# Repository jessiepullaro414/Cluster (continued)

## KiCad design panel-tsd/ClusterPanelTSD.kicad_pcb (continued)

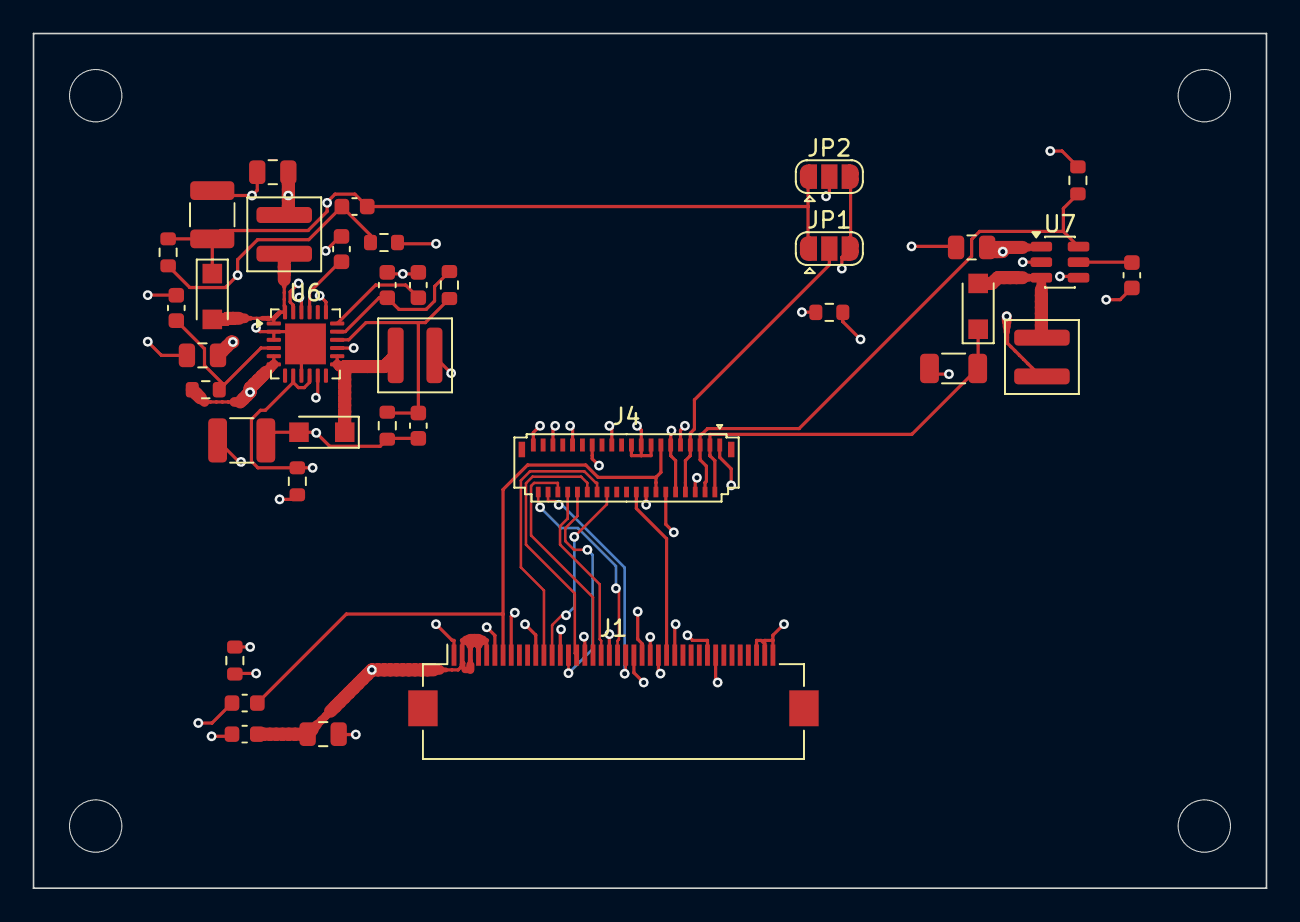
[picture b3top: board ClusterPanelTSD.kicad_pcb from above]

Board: 6 copper layers, 75.4 x 52.3 mm, 41 parts (0 on the bottom side), 32 nets.

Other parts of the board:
MH1, MH2, MH3, MH4: MountingHole_3.2mm_M3

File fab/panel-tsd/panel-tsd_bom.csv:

Manufacturer Part Number,Manufacturer,Quantity,Designators,Package,Category,Description,Status
PMEG6010ELRX,Nexperia,3,D2-D4,Nexperia_CFP3_SOD-123W,Semiconductors,"Boost rectifier Schottky, 60V/1A, SOD-123W",ok
(no part - PCB footprint only),-,2,"JP1, JP2",SolderJumper-3_P1.3mm_Open_RoundedPad1.0x1.5mm,Semiconductors,3-pad OPEN solder jumper (KiCad SolderJumper-3_P1.3mm_Open_RoundedPad1.0x1.5mm); bridged with a solder blob after verifying the panel's +/-6.5V pin polarity - see JP1/JP2 in build_schematic.py,ok
XAL4030-472MEC,Coilcraft,2,"L2, L3",L_Coilcraft_XAL4030-XXX,Semiconductors,"4.7uH shielded molded power inductor, Isat 4.6A, DCR 40mR typ, 4x4x3mm (datasheet Document 806-1; trailing C = 7in reel ordering code)",ok
TPS61165TDBVRQ1,TI,1,U7,SOT-23-6,Semiconductors,"Automotive boost white-LED driver, panel backlight 15V/180mA from +5V with PWM dimming, SOT-23-6 DBV (datasheet SLVSB73B); TI lists the family Active. Orderable suffix taken from a TI E2E thread and a datasheet listing - confirm on TI's store",ok
TPS65131TRGERQ1,TI,1,U6,HVQFN-24-1EP_4x4mm_P0.5mm_EP2.5x2.5mm,Semiconductors,"Automotive dual-output boost + inverting LCD bias supply, panel +6.5V/-6.5V analog rails from +5V, VQFN-24 RGE with wettable flanks (datasheet SLVSBB2F); TI lists it Active",ok
XAL4040-103MEC,Coilcraft,1,L4,L_Coilcraft_XAL4040-XXX,Semiconductors,"10uH shielded molded power inductor, Isat 3.0A, DCR 84mR typ, 4x4x4mm (datasheet Document 806-1; trailing C = 7in reel ordering code)",ok
FH12-40S-0.5SH(55),Hirose,1,J1,Hirose_FH12-40S-0.5SH_1x40-1MP_P0.50mm_Horizontal,Connectors,"Port input from the brain board's screen port A (MIPI DSI): 40-position 0.5 mm-pitch FFC connector, the same part as the brain board's J4, pin order in tools/screen_ports.py. PATTERN: confirm the (55) reel suffix and the 0.5 A per-contact rating in the cart",ok
FH26-39S-0.3SHW(99),Hirose,1,J4,Hirose_FH26-39S-0.3SHW_2Rows-39Pins-1MP_P0.60mm_Horizontal,Connectors,"39-position 0.3mm-pitch FPC connector for the TST040HDBC-42's 39-pin FPC. The panel datasheet does NOT name a connector: 0.3mm pitch is inferred from the FPC's 12mm width across 39 pins, and FH26 is bottom-contact - specify the FPC's exposed-pad side when ordering from TSD. Hirose lists the (05) variant obsolete and FH26W-39S-0.3SHW(60) as current: confirm its land pattern against the bundled FH26 footprint before ordering",ok
"FFC, 40-way 0.5 mm pitch, about 100-150 mm long (PATTERN: e.g. Molex 15015 series)",Molex / Wurth (TBD),1,J1 to the brain board's J4,FFC cable,Companion parts (ordered separately),The ribbon to the brain board's screen port A (it is listed on the brain board's BOM too: buy one per screen). Choose the contact orientation that joins contact n to contact n,ok
Team Source Display TST040HDBC-42,Team Source Display (TSD),1,plugs into J4,FPC module,Companion parts (ordered separately),"4.0in 720x720 round IPS, native MIPI-DSI (3 lanes), ICNL9707 driver built into the module, 800 cd/m2, -30..+80C, 101.52mm active circle - datasheet V1.0 (2023-06-29) read in full; connects via J4 above, not its own BOM line. Datasheet table and drawing DISAGREE on which FPC pins carry +6.5V vs -6.5V - resolve with TSD before bridging JP1/JP2. Order the FPC with the exposed-pad side matching J4's bottom-contact. ORDER FROM TSD (not a stocked distributor part): request the FPC with contact fingers matching J4 (Hirose FH26 is bottom-contact) and ask the questions in docs/rfq-drafts.md first",ok
AC0603FR-07100KL,Yageo,3,"R41, R43, R50",R_0603_1608Metric,Passives,"Resistor 100k 1% 0603 thick film, AEC-Q200 [PATTERN: confirm this exact part number in the distributor cart]",PATTERN: confirm in cart
GCM188R71H104KA57D,Murata,3,"C2, C3, C42",C_0603_1608Metric,Passives,"Capacitor, 100 nF X7R 50 V, AEC-Q200",ok
GCM188R71H224KA64D,Murata,2,"C43, C51",C_0603_1608Metric,Passives,"Capacitor, 220 nF X7R 50 V, AEC-Q200",ok
GCM21BR71A106KE22L,Murata,2,"C1, C50",C_0805_2012Metric,Passives,"Capacitor, 10 uF X7R 10 V, AEC-Q200",ok
GCM21BR71C475KA73L,Murata,2,"C40, C41",C_0805_2012Metric,Passives,"Capacitor, 4.7 uF X7R 16 V, AEC-Q200",ok
GCM32ER71C226ME19L,Murata,2,"C46, C47",C_1210_3225Metric,Passives,"Capacitor, 22 uF X7R 16 V, AEC-Q200",ok
AC0603FR-07100RL,Yageo,1,R37,R_0603_1608Metric,Passives,"Resistor 100R 1% 0603 thick film, AEC-Q200 [PATTERN: confirm this exact part number in the distributor cart]",PATTERN: confirm in cart
AC0603FR-07130KL,Yageo,1,R39,R_0603_1608Metric,Passives,"Resistor 130k 1% 0603 thick film, AEC-Q200 [PATTERN: confirm this exact part number in the distributor cart]",PATTERN: confirm in cart
AC0603FR-071R1L,Yageo,1,R42,R_0603_1608Metric,Passives,"Resistor 1R1 1% 0603 thick film, AEC-Q200 [PATTERN: confirm this exact part number in the distributor cart]",PATTERN: confirm in cart
AC0603FR-072KL,Yageo,1,R1,R_0603_1608Metric,Passives,"Resistor 2k 1% 0603 thick film, AEC-Q200 [PATTERN: confirm this exact part number in the distributor cart]",PATTERN: confirm in cart
AC0603FR-07499KL,Yageo,1,R40,R_0603_1608Metric,Passives,"Resistor 499k 1% 0603 thick film, AEC-Q200 [PATTERN: confirm this exact part number in the distributor cart]",PATTERN: confirm in cart
AC0603FR-07511KL,Yageo,1,R38,R_0603_1608Metric,Passives,"Resistor 511k 1% 0603 thick film, AEC-Q200 [PATTERN: confirm this exact part number in the distributor cart]",PATTERN: confirm in cart
GCJ31CC71H475KA01L,Murata,1,C52,C_1206_3216Metric,Passives,"Capacitor, 4.7 uF X7R 50 V, AEC-Q200",ok
GCM1885C1H120JA16D,Murata,1,C48,C_0603_1608Metric,Passives,"Capacitor, 12 pF C0G 50 V, AEC-Q200",ok
GCM1885C1H150JA16D,Murata,1,C49,C_0603_1608Metric,Passives,"Capacitor, 15 pF C0G 50 V, AEC-Q200 [PATTERN: confirm this exact part number in the distributor cart]",PATTERN: confirm in cart
GCM188R71H103KA37D,Murata,1,C44,C_0603_1608Metric,Passives,"Capacitor, 10 nF X7R 50 V, AEC-Q200",ok
GCM188R71H472KA37D,Murata,1,C45,C_0603_1608Metric,Passives,"Capacitor, 4.7 nF X7R 50 V, AEC-Q200",ok

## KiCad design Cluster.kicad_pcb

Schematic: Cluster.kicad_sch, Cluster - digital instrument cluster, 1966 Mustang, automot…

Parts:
C1: 10uF X7R (AEC-Q200); C_0603_1608Metric
C2: 22uF X7R (AEC-Q200); C_0603_1608Metric
C3: 1uF X7R (AEC-Q200); C_0603_1608Metric
C4, C5, C23, C24: 18pF (AEC-Q200); C_0603_1608Metric
C6, C7: 100nF (AEC-Q200); C_0603_1608Metric
C8: 1uF (AEC-Q200); C_0603_1608Metric
C10: 100nF charge-pump cap (AEC-Q200); C_0603_1608Metric
C11: 100nF BOOT cap (AEC-Q200); C_0603_1608Metric
C12: 1uF VCC decouple (AEC-Q200); C_0603_1608Metric
C13, C25: 100nF VCC decouple (AEC-Q200); C_0603_1608Metric
C14: 100nF VIO decouple (AEC-Q200); C_0603_1608Metric
C15: 100nF VBAT decouple (AEC-Q200); C_0603_1608Metric
C16: 4.7nF SPLIT stabilization (AEC-Q200); C_0603_1608Metric
C17, C18, C19, C20: 100nF VCI decouple (AEC-Q200); C_0603_1608Metric
C21: 10uF IN cap (AEC-Q200); C_0603_1608Metric
C22: 10uF OUT cap, real min 2.2uF per TI's own stabili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; C_0603_1608Metric
C26: 1uF VCC1V2 decouple (AEC-Q200); C_0603_1608Metric
C27: 100nF VCCIO decouple (AEC-Q200); C_0603_1608Metric
C28: 100nF ADC_FUEL smoothing (AEC-Q200); C_0603_1608Metric
C29: 100nF ADC_OIL smoothing (AEC-Q200); C_0603_1608Metric
C30: 100nF ADC_TEMP smoothing (AEC-Q200); C_0603_1608Metric
C31: 100nF ADC_BATT smoothing (AEC-Q200); C_0603_1608Metric
D1: SMCJ33A automotive (AEC-Q101); D_SMC
F1: Mini blade holder, 2A Littelfuse 297 fuse (SAE J2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; Fuseholder_Blade_Mini_Keystone_3568
J1: DTM06-2S nickel, 12V input (sealed); TerminalBlock_Phoenix_MKDS-1,5-2-5.08_1x02_P5.08mm_Horizont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
J2: SWD Tag-Connect; Tag-Connect_TC2030-IDC-NL_2x03_P1.27mm_Vertical
J3: Panox BH021WVC02 - center speedo; Amphenol_F32Q-1A7x1-11040_1x40-1MP_P0.5mm_Horizontal
L1: 10uH power (AEC-Q200); L_1210_3225Metric
L2: ferrite bead (AEC-Q200); L_1210_3225Metric
Q1: PMV37ENEA automotive (AEC-Q101); SOT-23
Q2: PMV37ENEA automotive (AEC-Q101) - shared aux-gaug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; SOT-23
Q3: PMV37ENEA automotive (AEC-Q101) - speedo backligh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; SOT-23
R1: 10k pull-up (AEC-Q200); R_0603_1608Metric
R2: 10k (AEC-Q200); R_0603_1608Metric
R3: 2.49k (AEC-Q200); R_0603_1608Metric
R4, R5: 60R split termination (AEC-Q200) - DNP unless bus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; R_0603_1608Metric
R6, R7, R8, R9: 120R VLED series (self-calculated for ~15mA at 5V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; R_0603_1608Metric
R10: 100R BL_EN gate resistor (AEC-Q200); R_0603_1608Metric
R11: 10k LPSPI2_SIN pull-down, idle-state definition (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; R_0603_1608Metric
R12: 7.32k FB divider top, self-calculated for 1.28V (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; R_0603_1608Metric
R13: 100k FB divider bottom, self-calculated for 1.28V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; R_0603_1608Metric
R14: 120R LEDA series (self-calculated, ~15mA at 5V - 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; R_0603_1608Metric
R15: 100R SPD_BL_PWM gate resistor (AEC-Q200); R_0603_1608Metric
R16: 47R fuel pull-up, self-calculated for the sender'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; R_0603_1608Metric
R17: 47R oil pressure pull-up, self-calculated for the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; R_0603_1608Metric
R18: 100R coolant temp pull-up, self-calculated for th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; R_0603_1608Metric
R19: 49.9k battery divider top, self-calculated for 9-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; R_0603_1608Metric
R20: 10k battery divider bottom, self-calculated for 9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; R_0603_1608Metric
U1: NXP S32K144 automotive (AEC-Q100); LQFP-64_10x10mm_P0.5mm
U2: LMR33630-Q1 (AEC-Q100 G1); TI_RNX0012C_VQFN-HR-12_2x3mm_P0.5mm
U3: LM74700-Q1 (AEC-Q100 G1); SOT-23-6
U4: TLV733P-Q1 (AEC-Q100 G1); SOT-23-5
U5: NXP TJA1043T automotive CAN transceiver (AEC-Q100); SOIC-14_3.9x8.7mm_P1.27mm
U6: Raystar RFA401280B-AYW-DNF1 - Fuel level gauge; Amphenol_F32Q-1A7x1-11018_1x18-1MP_P0.5mm_Horizontal
U7: Raystar RFA401280B-AYW-DNF1 - Oil pressure gauge; Amphenol_F32Q-1A7x1-11018_1x18-1MP_P0.5mm_Horizontal
U8: Raystar RFA401280B-AYW-DNF1 - Coolant temp gauge; Amphenol_F32Q-1A7x1-11018_1x18-1MP_P0.5mm_Horizontal
U9: Raystar RFA401280B-AYW-DNF1 - Battery voltage gau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; Amphenol_F32Q-1A7x1-11018_1x18-1MP_P0.5mm_Horizontal
U10: TPS7A16-Q1 (AEC-Q100 G1); Texas_DGN0008D_VSSOP-8-1EP_3x3mm_P0.65mm_EP2x2.94mm_Mask1.5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
U11: Bridgetek BT817AQ automotive (AEC-Q100 G2); QFN-64-1EP_9x9mm_P0.5mm_EP4.1x4.1mm
Y1: 8MHz (AEC-Q200); Crystal_SMD_3225-4Pin_3.2x2.5mm
Y2: 12MHz (AEC-Q200); Crystal_SMD_3225-4Pin_3.2x2.5mm

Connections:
+3V3: C3.1, C6.1, C7.1, C14.1, C17.1, C18.1, C19.1, C20.1, C21.1, C25.1, C27.1, J2.2 (VCC), J3.5 (VCI), L2.1, R1.1, R16.1, R17.1, R18.1, U1.7 (VDD), U1.41 (VDD), U4.5 (OUT), U5.5 (VIO), U6.16 (VCI3V3), U7.16 (VCI3V3), U8.16 (VCI3V3), U9.16 (VCI3V3), U10.5 (EN), U10.8 (IN), U11.9 (VCCIO1), U11.17 (VCCIO3), U11.24 (VCC), U11.27 (VCCA), U11.28 (VCCIO2)
+5V: C2.1, C13.1, L1.2, R2.1, R6.1, R7.1, R8.1, R9.1, R14.1, U4.1 (IN), U4.3 (EN), U5.3 (VCC)
ADC_BATT: C31.1, R19.2, R20.1, U1.47 (ADC_BATT)
ADC_FUEL: C28.1, R16.2, U1.50 (ADC_FUEL); also elsewhere on the board
ADC_OIL: C29.1, R17.2, U1.49 (ADC_OIL); also elsewhere on the board
ADC_TEMP: C30.1, R18.2, U1.48 (ADC_TEMP); also elsewhere on the board
AUX_CS0: U1.13 (AUX_CS0), U6.10 (CS)
AUX_CS1: U1.14 (AUX_CS1), U7.10 (CS)
AUX_CS2: U1.15 (AUX_CS2), U8.10 (CS)
AUX_CS3: U1.16 (AUX_CS3), U9.10 (CS)
AUX_DC0: U1.17 (AUX_DC0), U6.13 (RS)
AUX_DC1: U1.22 (AUX_DC1), U7.13 (RS)
AUX_DC2: U1.23 (AUX_DC2), U8.13 (RS)
AUX_DC3: U1.24 (AUX_DC3), U9.13 (RS)
AUX_RST: U1.42 (AUX_RST), U6.15 (RESET), U7.15 (RESET), U8.15 (RESET), U9.15 (RESET)
AUX_VLED_RTN: Q2.2 (S), U6.8 (VLED-), U7.8 (VLED-), U8.8 (VLED-), U9.8 (VLED-)
BL_EN: R10.1, U1.39 (BL_EN)
BL_GATE: Q2.1 (G), R10.2
BOOT_CAP: C11.1, U2.4 (BOOT)
BT817_PDN: U1.43 (BT817_PDN), U11.12 (PD_N)
BT817_X1: C23.1, U11.21 (X1), Y2.1 (X1), Y2.3 (X1)
BT817_X2: C24.1, U11.22 (X2), Y2.2 (X2), Y2.4 (X2)
CAN0_EN: U1.18 (CAN0_EN), U5.6 (EN)
CAN0_H: R4.1, U5.13 (CANH); also elsewhere on the board
CAN0_L: R5.2, U5.12 (CANL); also elsewhere on the board
CAN0_RX: U1.6 (CAN0_RX), U5.4 (RXD)
CAN0_SPLIT: C16.1, R4.2, R5.1, U5.11 (SPLIT)
CAN0_STB_N: U1.19 (CAN0_STB_N), U5.14 (STB_N)
CAN0_TX: U1.5 (CAN0_TX), U5.1 (TXD)
DE: J3.13 (DE), U11.35 (DE)
FB: R2.2, R3.1, U2.7 (FB)
FB1V2: R12.2, R13.1, U10.2 (FB)
GATE_DRV: Q1.1 (G), U3.5 (GATE)
GND: C1.2, C2.2, C3.2, C4.2, C5.2, C6.2, C7.2, C8.2, C12.2, C13.2, C14.2, C15.2, C16.2, C17.2, C18.2, C19.2, C20.2, C21.2, C22.2, C23.2, C24.2, C25.2, C26.2, C27.2, C28.2, C29.2, C30.2, C31.2, D1.2, J1.2 (GND), J2.6 (GND), J3.4 (GND), J3.34 (GND), J3.40 (GND), Q2.3 (D), Q3.3 (D), R3.2, R11.2, R13.2, R20.2, U1.10 (VSS), U1.40 (VSS), U2.1 (PGND), U2.6 (AGND), U2.11 (PGND), U3.2 (GND), U4.2 (GND), U5.2 (GND), U5.9 (WAKE), U6.5 (TP_GND), U6.9 (GND), U6.18 (GND), U7.5 (TP_GND), U7.9 (GND), U7.18 (GND), U8.5 (TP_GND), U8.9 (GND), U8.18 (GND), U9.5 (TP_GND), U9.9 (GND), U9.18 (GND), U10.4 (GND), U10.9 (EP), U11.18 (SPIM_MISO), U11.23 (GND), U11.33 (GND), U11.48 (GND), U11.65 (EP)
HSYNC: J3.15 (HSYNC), U11.37 (HSYNC)
J3_LEDA: J3.1 (LEDA), R14.2
LPSPI1_CS: U1.45 (LPSPI1_CS), U11.6 (CS_N)
LPSPI1_SCK: U1.2 (LPSPI1_SCK), U11.3 (SCK)
LPSPI1_SIN: U1.1 (LPSPI1_SIN), U11.4 (MISO)
LPSPI1_SOUT: U1.46 (LPSPI1_SOUT), U11.5 (MOSI)
LPSPI2_SCK: U1.29 (LPSPI2_SCK), U6.11 (SCL), U7.11 (SCL), U8.11 (SCL), U9.11 (SCL)
LPSPI2_SIN: R11.1, U1.26 (LPSPI2_SIN)
LPSPI2_SOUT: U1.25 (LPSPI2_SOUT), U6.12 (SDA), U7.12 (SDA), U8.12 (SDA), U9.12 (SDA)
OSC_IN: C4.1, U1.11 (OSC_IN), Y1.1 (OSC_IN), Y1.3 (OSC_IN)
OSC_OUT: C5.1, U1.12 (OSC_OUT), Y1.2 (OSC_OUT), Y1.4 (OSC_OUT)
PCLK: J3.12 (PCLK), U11.39 (PCLK)
RESET: J2.5 (RST), R1.2, U1.63 (RESET)
SPD_B2: J3.16 (DB0), U11.45 (B2)
SPD_B3: J3.17 (DB1), U11.44 (B3)
SPD_B4: J3.18 (DB2), U11.43 (B4)
SPD_B5: J3.19 (DB3), U11.42 (B5)
SPD_B6: J3.20 (DB4), U11.41 (B6)
SPD_B7: J3.21 (DB5), U11.40 (B7)
SPD_BL_GATE: Q3.1 (G), R15.2
SPD_BL_PWM: R15.1, U11.34 (BACKLIGHT)
SPD_G2: J3.22 (DB6), U11.54 (G2)
SPD_G3: J3.23 (DB7), U11.53 (G3)
SPD_G4: J3.24 (DB8), U11.52 (G4)
SPD_G5: J3.25 (DB9), U11.51 (G5)
SPD_G6: J3.26 (DB10), U11.50 (G6)
SPD_G7: J3.27 (DB11), U11.49 (G7)
SPD_R2: J3.28 (DB12), U11.63 (R2)
SPD_R3: J3.29 (DB13), U11.62 (R3)
SPD_R4: J3.30 (DB14), U11.61 (R4)
SPD_R5: J3.31 (DB15), U11.60 (R5)
SPD_R6: J3.32 (DB16), U11.59 (R6)
SPD_R7: J3.33 (DB17), U11.58 (R7)
SPD_VLED_RTN: J3.2 (LEDK), J3.3 (LEDK), Q3.2 (S)
ST7701_CS: J3.11 (CS), U11.10 (GPIO2)
ST7701_RESET: J3.6 (RESET), U11.13 (GPIO3)
ST7701_SCK: J3.10 (SCK), U11.8 (GPIO1)
ST7701_SDA: J3.9 (SDA), U11.7 (GPIO0)
SW: C11.2, L1.1, U2.3 (NC), U2.12 (SW)
SWCLK: J2.3 (SWCLK), U1.62 (SWCLK)
SWDIO: J2.1 (SWDIO), U1.64 (SWDIO)
U6_VLED: R6.2, U6.7 (VLED+)
U7_VLED: R7.2, U7.7 (VLED+)
U8_VLED: R8.2, U8.7 (VLED+)
U9_VLED: R9.2, U9.7 (VLED+)
VCAP: C10.1, U3.1 (VCAP)
VCC1V2: C22.1, C26.1, R12.1, U10.1 (OUT), U11.2 (VCC1V2), U11.25 (VCC1V2), U11.57 (VCC1V2)
VCC_INT: C12.1, U2.5 (VCC)
VDDA: C8.1, L2.2, U1.8 (VDDA), U1.9 (VREFH)
VIN: F1.1, J1.1 (VIN)
VIN_FUSED: C10.2, F1.2, Q1.2 (S), U3.3 (EN), U3.6 (ANODE)
VIN_PROT: C1.1, C15.1, D1.1, Q1.3 (D), R19.1, U2.2 (VIN), U2.9 (EN), U2.10 (VIN), U3.4 (CATHODE), U5.10 (VBAT)
VSYNC: J3.14 (VSYNC), U11.36 (VSYNC)

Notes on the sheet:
own S32K1xx Data Sheet Rev.15): this part has 3x LPSPI, 3x FlexCAN (1 w/ FD),
5. Value fields tag automotive qualification: Q100 G1 = AEC-Q100 Grade 1 (ICs) -
Q101 = AEC-Q101 (discretes) - Q200 = AEC-Q200 (passives).
3. U1 pin numbers are REAL, verified against NXP's S32K1xx Reference Manual (same
generic placeholders. ONLY fixed pins (crystal/SWD/RESET/power) are wired this
BT817AQ QSPI + CAN0 + 4x ADC will need fit comfortably inside the ~58 GPIO this
researched pin-by-pin, that's the next real work before those subsystems wire.
SWCLK pin_not_driven - genuinely driven off-sheet by the debug probe).
5V BUCK + 3.3V LDO
manifold-pcb/thermo-pcb's own proven, real circuit - not re-derived here.
POWER INPUT, REVERSE-BATTERY + TRANSIENT PROTECTION
NOTES:
MCU CORE (NXP S32K144, 3.3V LOGIC) - FIXED PINS ONLY
2x12-bit ADC x16ch=32 channels - the ~26 real pins Cluster's aux-gauge SPI bus +
CAN0: NXP TJA1043T TRANSCEIVER (PLAN STEP 2)
SENSOR ADC FRONT END: FUEL / OIL / TEMP / BATTERY (PLAN STEP 5)
4. Real S32K144 pin/peripheral budget (README.md, verified 2026-09-22 against NXP's
drawn wires, with local labels only where pins are legitimately shared.
64-pin package leaves after the fixed pins wired here - NOT yet pin-mux
2. Power stage (F1/Q1/U2/U3/U4 + supporting passives) reused VERBATIM from
1. Power nets (+5V, +3V3, GND, VIN) use power symbols throughout; signal nets use
BT817AQ + ST7701S SPEEDO MODULE (PLAN STEP 4)
pigtail strategy as a starting point - not yet re-confirmed as the right choice
power_pin_not_driven - ERC can't trace power through a ferrite/FET/diode; J2
for a dash-mounted (not engine-bay) board; flagged for the connector pass.
research thermo-pcb/manifold-pcb already did for this exact part/package) - not
7. kicad-cli sch erc is expected to show only the same tool-limitation findings
pass - see this file's own header docstring for what's deliberately deferred.
every sibling board's schematic has at this stage (VDDA/U2-VIN/+5V
4x GC9A01 AUX GAUGES: FUEL / OIL / COOLANT TEMP / BATTERY (PLAN STEP 3)
6. J1 (power landing) reuses thermo-pcb's real Phoenix MKDS + outboard DTM06-2S

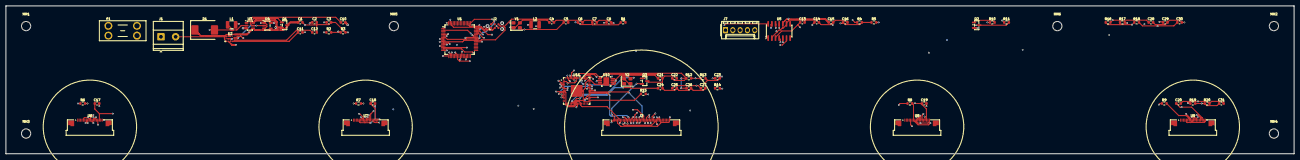
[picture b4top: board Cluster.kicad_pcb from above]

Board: 4 copper layers, 447.1 x 51.3 mm, 80 parts (0 on the bottom side), 87 nets.

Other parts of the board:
J7: DTM06-5S nickel, CAN0 + 3x sender input (sealed); Molex_KK-254_AE-6410-05A_1x05_P2.54mm_Vertical
MH1, MH2, MH3, MH4, MH5, MH6: MountingHole_3.2mm_M3

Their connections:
ADC_FUEL: J7.3; also elsewhere on the board
ADC_OIL: J7.4; also elsewhere on the board
ADC_TEMP: J7.5; also elsewhere on the board
CAN0_H: J7.1; also elsewhere on the board
CAN0_L: J7.2; also elsewhere on the board

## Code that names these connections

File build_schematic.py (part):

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#     own real pull-down, R11, in the placement section below), SOUT=
#     pin25(PTC1), PCS0=pin30(PTC14, claimed here but marked no_connect
#     in the placement section - each of the 4 displays needs its OWN
#     chip select, so 4 individual bit-banged GPIO (AUX_CS0-3) are used
#     instead of this single hardware PCS0 pin).
#   - FlexCAN0: RX=pin6(PTE4), TX=pin5(PTE5).
#   - 4x ADC channel (split across the real ADC0/ADC1 instances, which
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#     mode control) - none of these need a specific peripheral function,
#     so any confirmed-free GPIO-capable pin works: CS0=pin13(PTE3),
#     CS1=pin14(PTD16), CS2=pin15(PTD15), CS3=pin16(PTE9), DC0=pin17(PTE8),
#     DC1=pin22(PTD7), DC2=pin23(PTD6), DC3=pin24(PTD5), AUX_RST=pin42
#     (PTB13), BL_EN=pin39(PTE7), BT817_PDN=pin43(PTB12), CAN0_EN=pin18
#     (PTB5), CAN0_STB_N=pin19(PTB4) - the latter two added in plan Step 2
#     alongside the TJA1043T transceiver itself, same real EN+STB_N mode-
#     control pattern ecu-pcb's own TJA1043T wiring already established
#     (real 4-state mode select, not a single 3-state pin - see that
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# ecu-pcb's own research), VBAT->VIN_PROT (the always-on protected rail,
# NOT the relay-gated one, so a CAN bus-wake event can revive the board
# with ignition off - same real automotive reasoning), TXD/RXD wired to
# the MCU's CAN0_TX/CAN0_RX pins (matching net NAME, not geometric
# alignment - same trick Thermo used for its own MCU<->ADC link), EN/
# STB_N to real MCU GPIO (4-state mode select, not a single 3-state pin -
# see ecu-pcb's own registration comment for the full reasoning), INH/
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#   - CTP_* (capacitive touch controller interface, pins 29-32): no
#     touch controller on this design (the BH021WVC02 module's own touch
#     pins are likewise left no_connect below) - all 4 left no_connect.
#   - GPIO0-2 are real, deliberately claimed for the module's 3-wire
#     serial interface (SDA/SCK/CS, per the BH021WVC02's own real pin
#     table - confirmed only 3 signal pins, no separate D/CX pin, since
#     ST7701S's 3-line serial mode embeds D/CX in the bit stream itself).
#     GPIO3 drives the module's own real RESET pin (active-low, per its
#     datasheet) - a hard reset line genuinely can't be left floating, so
#     this spare GPIO gets a real job rather than staying unused. INT_N
#     is genuinely unused this pass (real spare capacity, no async event
#     this design needs to react to yet) - left no_connect.
#   - PD_N connects to the real BT817_PDN pin already claimed on U1 back
#     in plan Step 1.
register_symbol(f"{LIB}:BT817AQ", "U", "Bridgetek BT817AQ automotive (AEC-Q100 G2)",
                "Package_DFN_QFN:QFN-64-1EP_9x9mm_P0.5mm_EP4.1x4.1mm",
                {'L': [P(3, "SCK", "input"), P(4, "MISO", "output"),
                       P(5, "MOSI", "input"), P(6, "CS_N", "input"),
                       P(12, "PD_N", "input"), P(11, "INT_N", "no_connect"),
                       P(7, "GPIO0", "output"), P(8, "GPIO1", "output"),
                       P(10, "GPIO2", "output"), P(13, "GPIO3", "output")],
                 'R': [P(35, "DE", "output"), P(36, "VSYNC", "output"),
                       P(37, "HSYNC", "output"), P(38, "DISP", "output"),
                       P(39, "PCLK", "output"), P(34, "BACKLIGHT", "output")],
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      conn={'1': ('pwr', 'VIN'), '2': ('wire',)})
place(f"{LIB}:MOSFET_N", "Q1", "PMV37ENEA automotive (AEC-Q101)", 85, RAIL,
      conn={'2': ('wire',), '3': ('wire',),
            '1': ('label', 'GATE_DRV', 7.62)})
place(f"{LIB}:IC_IdealDiode", "U3", "LM74700-Q1 (AEC-Q100 G1)", 85, 85,
      conn={'6': ('label', 'VIN_FUSED', 5.08),
            '2': ('pwr', 'GND', 7.62),
            '5': ('label', 'GATE_DRV', 5.08), '4': ('label', 'VIN_PROT', 5.08),
            '3': ('label', 'VIN_FUSED', 5.08), '1': ('label', 'VCAP', 5.08)})
place(f"{LIB}:C_V", "C10", "100nF charge-pump cap (AEC-Q200)", 60, 100,
      conn={'1': ('label', 'VCAP'), '2': ('label', 'VIN_FUSED')})
place(f"{LIB}:TVS_V", "D1", "SMCJ33A automotive (AEC-Q101)", 113, 70,
      conn={'1': ('label', 'VIN_PROT'), '2': ('pwr', 'GND')})
place(f"{LIB}:C_V", "C1", "10uF X7R (AEC-Q200)", 150, 70,
      conn={'1': ('label', 'VIN_PROT'), '2': ('pwr', 'GND')})

vin_x, vin_y = pin_pos[("F1", "1")]
place_pwr_flag("VIN", vin_x, snap(vin_y - 10))
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
y_u2 = RAIL - off(f"{LIB}:IC_Buck", 2)[1]
place(f"{LIB}:IC_Buck", "U2", "LMR33630-Q1 (AEC-Q100 G1)", 170, y_u2,
      conn={'2': ('wire',), '10': ('label', 'VIN_PROT', 5.08),
            '1': ('pwr', 'GND', 5.08), '11': ('pwr', 'GND', 5.08),
            '12': ('wire',), '4': ('label', 'BOOT_CAP'),
            '7': ('label', 'FB'), '9': ('label', 'VIN_PROT', 5.08),
            '5': ('label', 'VCC_INT'), '8': ('nc',),
            '6': ('pwr', 'GND'), '3': ('label', 'SW')})
place(f"{LIB}:C_V", "C11", "100nF BOOT cap (AEC-Q200)", 195, 90,
      conn={'1': ('label', 'BOOT_CAP'), '2': ('label', 'SW')})
place(f"{LIB}:C_V", "C12", "1uF VCC decouple (AEC-Q200)", 218, 90,
      conn={'1': ('label', 'VCC_INT'), '2': ('pwr', 'GND')})
y_l1 = pin_pos[("U2", "12")][1] - off(f"{LIB}:L_H", 1)[1]
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place(f"{LIB}:C_V", "C3", "1uF X7R (AEC-Q200)", 305, 70,
      conn={'1': ('pwr', '+3V3'), '2': ('pwr', 'GND')})

wire_pins("F1", 2, "Q1", 2, label="VIN_FUSED")
wire_pins("Q1", 3, "U2", 2, label="VIN_PROT")
wire_pins("U2", 12, "L1", 1, label="SW")

# --- MCU core (fixed pins only) ---
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            # LPSPI2's real hardware PCS0 (pin 30) is genuinely unused by
            # design (plan Step 3): the 4 GC9A01 aux gauges share one SPI
            # bus but each needs its OWN chip select, so 4 individual
            # bit-banged GPIO (AUX_CS0-3) are used instead of the single
            # hardware PCS0 - a real, deliberate choice, not an oversight,
            # documented with a real no-connect flag rather than left as
            # a dangling same-named label (same established distinction
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y_y1 = pin_pos[("U1", "11")][1] - off(f"{LIB}:XTAL", 1)[1]
place(f"{LIB}:XTAL", "Y1", "8MHz (AEC-Q200)", 65, y_y1,
      conn={'1': ('wire',), '2': ('wire',),
            '3': ('label', 'OSC_IN'), '4': ('label', 'OSC_OUT')})
wire_pins("Y1", 1, "U1", 11, label="OSC_IN")
wire_pins("Y1", 2, "U1", 12, label="OSC_OUT")
place(f"{LIB}:C_V", "C4", "18pF (AEC-Q200)", 45, y_y1 + 30,
      conn={'1': ('label', 'OSC_IN'), '2': ('pwr', 'GND')})
place(f"{LIB}:C_V", "C5", "18pF (AEC-Q200)", 68, y_y1 + 30,
      conn={'1': ('label', 'OSC_OUT'), '2': ('pwr', 'GND')})

place(f"{LIB}:C_V", "C6", "100nF (AEC-Q200)", 150, 190,
      conn={'1': ('pwr', '+3V3'), '2': ('pwr', 'GND')})
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place(f"{LIB}:TJA1043T", "U5", "NXP TJA1043T automotive CAN transceiver (AEC-Q100)",
      400, 250,
      conn={'3': ('pwr', '+5V', 5.08), '5': ('pwr', '+3V3', 5.08),
            '10': ('label', 'VIN_PROT', 5.08), '2': ('pwr', 'GND', 2.54),
            '1': ('label', 'CAN0_TX', 7.62), '4': ('label', 'CAN0_RX', 7.62),
            '6': ('label', 'CAN0_EN', 7.62), '14': ('label', 'CAN0_STB_N', 7.62),
            '7': ('nc',), '8': ('nc',),
            '9': ('pwr', 'GND', 5.08),
            '11': ('label', 'CAN0_SPLIT'),
            '12': ('label', 'CAN0_L', 7.62), '13': ('label', 'CAN0_H', 7.62)})
place(f"{LIB}:C_V", "C13", "100nF VCC decouple (AEC-Q200)", 370, 220,
      conn={'1': ('pwr', '+5V'), '2': ('pwr', 'GND')})
place(f"{LIB}:C_V", "C14", "100nF VIO decouple (AEC-Q200)", 345, 220,
      conn={'1': ('pwr', '+3V3'), '2': ('pwr', 'GND')})
place(f"{LIB}:C_V", "C15", "100nF VBAT decouple (AEC-Q200)", 320, 220,
      conn={'1': ('label', 'VIN_PROT'), '2': ('pwr', 'GND')})
place(f"{LIB}:R_V", "R4", "60R split termination (AEC-Q200) - DNP unless bus end-node",
      550, 230,
      conn={'1': ('label', 'CAN0_H'), '2': ('label', 'CAN0_SPLIT')})
place(f"{LIB}:R_V", "R5", "60R split termination (AEC-Q200) - DNP unless bus end-node",
      550, 260,
      conn={'1': ('label', 'CAN0_SPLIT'), '2': ('label', 'CAN0_L')})
place(f"{LIB}:C_V", "C16", "4.7nF SPLIT stabilization (AEC-Q200)", 580, 245,
      conn={'1': ('label', 'CAN0_SPLIT'), '2': ('pwr', 'GND')})
# CAN0_TX/CAN0_RX/CAN0_EN/CAN0_STB_N connect to U1 purely by matching net
# NAME (both symbols already use these exact same label strings on their
# own respective pins) - same trick thermo-pcb used for its MCU<->ADC
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for i, (u_ref, cs_label, dc_label, role) in enumerate(AUX_GAUGES):
    x0 = 30 + i * 120
    place(f"{LIB}:GC9A01_MODULE", u_ref, f"Raystar RFA401280B-AYW-DNF1 - {role} gauge", x0, 480,
          conn={'10': ('label', cs_label), '11': ('label', 'LPSPI2_SCK'),
                '12': ('label', 'LPSPI2_SOUT'), '13': ('label', dc_label),
                '15': ('label', 'AUX_RST'), '14': ('nc',),
                '7': ('label', f'{u_ref}_VLED', 5.08), '8': ('label', 'AUX_VLED_RTN', 5.08),
                # VCI3V3's power-symbol riser (a 'pwr' connection on an L/R
                # side climbs one extra PITCH) would otherwise land exactly
                # on pin 8's own 5.08 stub endpoint (adjacent R-side pins,
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# this part's real multi-amp rating.
place(f"{LIB}:MOSFET_N", "Q2", "PMV37ENEA automotive (AEC-Q101) - shared aux-gauge backlight switch",
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
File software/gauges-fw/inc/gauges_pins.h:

#ifndef GAUGES_PINS_H
#define GAUGES_PINS_H
/*
 * Pin claims for gauges/ rev C. Numbers are the 64-LQFP package pins; port
 * names are from NXP's S32K1xx IO table as recorded in
 * ../../gauges/build_schematic.py (single source of truth, regenerate this
 * file from it if the schematic changes).
 */

/* car bus, FlexCAN0 */
#define PIN_CAN0_RX        6   /* PTE4 */
#define PIN_CAN0_TX        5   /* PTE5 */
#define PIN_CAN0_EN        18  /* PTB5, TJA1043T EN */
#define PIN_CAN0_STB_N     19  /* PTB4, TJA1043T STB_N */
/* private link to display/, FlexCAN1 */
#define PIN_CAN1_RX        52  /* PTC6 */
#define PIN_CAN1_TX        51  /* PTC7 */
#define PIN_CAN1_STB       60  /* PTE0, TCAN1044V standby */

/* timer capture (FTM1) */
#define PIN_SPEED_IN       58  /* PTA10, FTM1_CH4, Hall speed pulses */
#define PIN_TACH_IN        57  /* PTA11, FTM1_CH5, tach pulses */
#define PIN_VR_SPEED_IN    56  /* PTA12, FTM1_CH6, comparator output of the two-wire VR speed input (J12, U13) */

/* ignition: pin interrupt, wakes the part from STOP/VLPS */
#define PIN_IGN_SENSE      59  /* PTE1 */

/* resistive senders and battery (ADC) */
#define PIN_ADC_FUEL       50  /* PTA0, ADC0_SE0 */
#define PIN_ADC_OIL        49  /* PTA1, ADC0_SE1 */
#define PIN_ADC_TEMP       48  /* PTA2, ADC1_SE0 */
#define PIN_ADC_BATT       47  /* PTA3, ADC1_SE1 */
#define PIN_DIM_ADC        31  /* PTB3, ADC0_SE7, dash dimmer feed */
/* review 2026-11-03: sender excitation (U11 ON), the senders' ADC bias, the switched 12 V pull-up / Hall supply (U12 IN) */
#define PIN_SENDER_EXC_EN  46  /* PTD2, U11 ON: the sender pull-ups on; low (R94) while the MCU resets */
#define PIN_SENDER_BIAS    53  /* PTE6, 6.8 k bias on the three sender ADC pins; high while awake, low in VLPS */
#define PIN_VPULL_EN       54  /* PTE2, U12 IN (through 10 k): VPULL on; low in VLPS */
#define PIN_DIM_LOAD_EN    32  /* PTB2, Q4 base through R106: the dash dimmer's test load on; low in VLPS */

/* six 12 V-active indicator lamps (active-low if the DNP pull-up is fitted) */
#define PIN_LAMP_TURN_L    35  /* PTC9 */
#define PIN_LAMP_TURN_R    36  /* PTC8 */
#define PIN_LAMP_HIGH_BEAM 37  /* PTA7 */
#define PIN_LAMP_BRAKE     38  /* PTA6 */
#define PIN_LAMP_ALT       43  /* PTB12 */
#define PIN_LAMP_OIL       44  /* PTD4 */

/* four GC9A01 aux gauges on LPSPI2 */
#define PIN_LPSPI2_SCK     29  /* PTC15 */
#define PIN_LPSPI2_SIN     26  /* PTC0 */
#define PIN_LPSPI2_SOUT    25  /* PTC1 */
#define PIN_LPSPI2_PCS0    30  /* PTC14 (claimed, unused: chip selects are GPIO) */
#define PIN_AUX_CS0        13  /* PTE3 */
#define PIN_AUX_CS1        14  /* PTD16 */
#define PIN_AUX_CS2        15  /* PTD15 */
#define PIN_AUX_CS3        16  /* PTE9 */
#define PIN_AUX_DC0        17  /* PTE8 */
#define PIN_AUX_DC1        22  /* PTD7 */
#define PIN_AUX_DC2        23  /* PTD6 */
#define PIN_AUX_DC3        24  /* PTD5 */
#define PIN_AUX_RST        42  /* PTB13 */
#define PIN_BL_EN          39  /* PTE7, aux backlight switch */

/* debug */
#define PIN_SWDIO          64  /* PTA4 */
#define PIN_SWCLK          62  /* PTC4 */

#endif

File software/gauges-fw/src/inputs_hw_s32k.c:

/* Register layer for the pulse, lamp and ignition inputs: FTM1 input capture (RM chapter 47), GPIO (chapter 12), PORT, PCC.
 * Written from the RM; compiled and linked for the S32K144, NEVER RUN on a part. */
#include "capture.h"
#include "gauges_pins.h"
#include "inputs_hw.h"
#include "s32k144_irq.h"
#include "s32k144_regs.h"
#include "senders.h"

typedef struct { uint8_t port, pin; } pin_t;

/* port and pin of each input (the comment tag is what tools/check_pins.py compares with gauges_pins.h) */
static const pin_t LAMP_PINS[LAMP_COUNT] = {
    { PORTC, 9 },    /* PIN_LAMP_TURN_L */
    { PORTC, 8 },    /* PIN_LAMP_TURN_R */
    { PORTA, 7 },    /* PIN_LAMP_HIGH_BEAM */
    { PORTA, 6 },    /* PIN_LAMP_BRAKE */
    { PORTB, 12 },   /* PIN_LAMP_ALT */
    { PORTD, 4 },    /* PIN_LAMP_OIL */
};
static const pin_t IGN_PIN = { PORTE, 1 };      /* PIN_IGN_SENSE */
static const pin_t SPEED_PIN = { PORTA, 10 };   /* PIN_SPEED_IN */
static const pin_t TACH_PIN = { PORTA, 11 };    /* PIN_TACH_IN */
static const pin_t VR_SPEED_PIN = { PORTA, 12 }; /* PIN_VR_SPEED_IN */
/* review 2026-11-03: outputs */
static const pin_t SENDER_EXC_PIN = { PORTD, 2 };   /* PIN_SENDER_EXC_EN */
static const pin_t SENDER_BIAS_PIN = { PORTE, 6 };  /* PIN_SENDER_BIAS */
static const pin_t VPULL_PIN = { PORTE, 2 };        /* PIN_VPULL_EN */
static const pin_t DIM_LOAD_PIN = { PORTB, 2 };     /* PIN_DIM_LOAD_EN */

#define FTM1_SPEED_CH 4u        /* FTM1_CH4 on PTA10, PORT mux alt 2 (IO signal table) */
#define FTM1_TACH_CH  5u        /* FTM1_CH5 on PTA11, PORT mux alt 2 */
#define FTM1_VR_CH    6u        /* FTM1_CH6 on PTA12, PORT mux alt 2 */

static volatile uint16_t g_overflows;           /* counts TOF in the overflow interrupt */
static uint32_t g_saved_primask;

static void gpio_input(pin_t p)
{
    PCC_PORT(p.port) = PCC_CGC;
    PORT_PCR(p.port, p.pin) = PORT_MUX(1);      /* GPIO, no internal pull: the board has its own divider (and DNP pull-up) */
    GPIO_PDDR(p.port) &= ~(1u << p.pin);
}

static void ftm_pin(pin_t p)
{
    PCC_PORT(p.port) = PCC_CGC;
    PORT_PCR(p.port, p.pin) = PORT_MUX(2);
}

static void gpio_output(pin_t p, bool high)
{
    PCC_PORT(p.port) = PCC_CGC;
    if (high) GPIO_PSOR(p.port) = 1u << p.pin; else GPIO_PCOR(p.port) = 1u << p.pin;   /* level first, then drive it */
    PORT_PCR(p.port, p.pin) = PORT_MUX(1);
    GPIO_PDDR(p.port) |= 1u << p.pin;
}

static void sender_excite(bool on)
{
    if (on) GPIO_PSOR(SENDER_EXC_PIN.port) = 1u << SENDER_EXC_PIN.pin;
    else GPIO_PCOR(SENDER_EXC_PIN.port) = 1u << SENDER_EXC_PIN.pin;
}

const sender_hw_t sender_hw_s32k = { sender_excite };

static void dim_load(bool on)
{
    if (on) GPIO_PSOR(DIM_LOAD_PIN.port) = 1u << DIM_LOAD_PIN.pin;
    else GPIO_PCOR(DIM_LOAD_PIN.port) = 1u << DIM_LOAD_PIN.pin;
}

void inputs_hw_init(void)
{
    /* review 2026-11-03: the 12 V pull-up rail (lamp/tach pull-ups, Hall sender supply) and the senders' ADC bias are on while
     * the MCU is awake; senders.c chops the excitation. power_hw_s32k.c turns all three off before VLPS. */
    gpio_output(VPULL_PIN, true);
    gpio_output(SENDER_BIAS_PIN, true);
    gpio_output(SENDER_EXC_PIN, true);
    gpio_output(DIM_LOAD_PIN, false);
    for (unsigned i = 0; i < LAMP_COUNT; i++) gpio_input(LAMP_PINS[i]);
    gpio_input(IGN_PIN);
    ftm_pin(SPEED_PIN);
    ftm_pin(TACH_PIN);
    ftm_pin(VR_SPEED_PIN);

    /* 8 MHz crystal -> SOSCDIV1 (divide by 1) -> FTM1 input clock, prescaled by 8 -> 1 MHz: one count is one microsecond. */
    SCG_SOSCDIV = (SCG_SOSCDIV & ~0x7u) | SCG_SOSCDIV1(1);
    PCC_FTM1 = 0u;                                          /* PCS is writable only while the clock gate is off */
    PCC_FTM1 = PCC_PCS(PCC_PCS_SOSCDIV1) | PCC_CGC;
    FTM1_SC = 0u;                                           /* counter stopped while it is set up */
    FTM1_MODE = 0x4u;                                       /* WPDIS (reset value), FTMEN off */
    FTM1_CNTIN = 0u;
    FTM1_MOD = 0xFFFFu;
    FTM1_CNT = 0u;
    FTM1_CNSC(FTM1_SPEED_CH) = FTM_CNSC_CHIE | FTM_CNSC_ELSA;
    FTM1_CNSC(FTM1_TACH_CH) = FTM_CNSC_CHIE | FTM_CNSC_ELSA;
    FTM1_CNSC(FTM1_VR_CH) = FTM_CNSC_CHIE | FTM_CNSC_ELSA;
    NVIC_ENABLE(FTM1_OVF_RELOAD_IRQn);
    NVIC_ENABLE(FTM1_CH4_5_IRQn);
    NVIC_ENABLE(FTM1_CH6_7_IRQn);
    FTM1_SC = FTM_SC_TOIE | FTM_SC_CLKS_SYS | FTM_SC_PS(3);   /* starts the counter */
}

/* ---- interrupts ---------------------------------------------------------------------------------------------- */

void FTM1_OVF_RELOAD_IRQHandler(void)
{
    uint32_t sc = FTM1_SC;
    if (sc & FTM_SC_TOF) {
        FTM1_SC = sc & ~FTM_SC_TOF;             /* read with TOF set, then write 0 (RM 47.3.3) */
        g_overflows++;
    }
}

/* A capture's 32-bit time: read the captured value first, then the overflow flag; a flag still set with a value in the low
 * half of the range means the capture came after the wrap whose interrupt has not run yet (capture_extend). */
static uint32_t extended(uint16_t cnv)
{
    bool tof = (FTM1_SC & FTM_SC_TOF) != 0u;
    return capture_extend(g_overflows, tof, cnv);
}

static void service_capture(unsigned ch)
{
    uint32_t sc = FTM1_CNSC(ch);
    if (sc & FTM_CNSC_CHF) {
        uint16_t v = (uint16_t)FTM1_CNV(ch);
        uint32_t t = extended(v);
        FTM1_CNSC(ch) = sc & ~FTM_CNSC_CHF;
        inputs_on_capture(ch - FTM1_SPEED_CH, t);       /* CH4, CH5, CH6: inputs_on_capture's channels 0, 1, 2 */
    }
}

void FTM1_CH4_5_IRQHandler(void)
{
    service_capture(FTM1_SPEED_CH);
    service_capture(FTM1_TACH_CH);
}

void FTM1_CH6_7_IRQHandler(void)
{
    service_capture(FTM1_VR_CH);
}

/* ---- the ops the logic uses ---------------------------------------------------------------------------------- */

static void lock(void) { __asm volatile("mrs %0, primask\n cpsid i" : "=r"(g_saved_primask) :: "memory"); }
static void unlock(void) { __asm volatile("msr primask, %0" :: "r"(g_saved_primask) : "memory"); }

static uint32_t now_us(void)
{
    lock();
    uint16_t cnt = (uint16_t)FTM1_CNT;
    uint32_t t = extended(cnt);
    unlock();
    return t;
}

static uint8_t lamps_raw(void)
{
    uint8_t m = 0;
    for (unsigned i = 0; i < LAMP_COUNT; i++)
        if (GPIO_PDIR(LAMP_PINS[i].port) & (1u << LAMP_PINS[i].pin)) m |= (uint8_t)(1u << i);
    return m;
}

static bool ign_raw(void) { return (GPIO_PDIR(IGN_PIN.port) & (1u << IGN_PIN.pin)) != 0u; }

const inputs_hw_t inputs_hw_s32k = { now_us, lamps_raw, ign_raw, lock, unlock, dim_load };

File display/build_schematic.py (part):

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    # config bus, and there is no bridge on this board anymore (direct
    # DSI to the panel - see build_panel()'s own docstring). They fall
    # through to bank C's genuinely-unused pins.
    "GPIO_9_DSI": "DSI_PANEL_EN",
    # Rotary dial (2026-10-02): a 360-degree potentiometer with a push
    # switch, the way automakers add a controller to a screen with no touch.
    # The wiper reads on Verdin ADC_1 (X1 pin 2, ADC_IN0; the datasheet's
    # absolute maximum for ADC pins is 2.1 V, so the pot is powered from the
    # 1.8 V rail), the click on GPIO_1 (X1 pin 206, 1.8 V logic).
    "ADC_1": "DIAL_ADC",
    "GPIO_1": "DIAL_CLICK",
    # CTRL_SLEEP_MOCI# (X1 pin 256) is the module's "enable for carrier
    # peripherals that must be turned off during sleep" (datasheet), 1.8 V.
    # It switches the dial sensor's 5 V supply.
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    # GPIO (GPIO1_IO10). Active-low by name (the # suffix); software picks
    # the edge. Driven by the ignition network in build_control().
    "CTRL_WAKE1_MICO#": "IGN_WAKE_N",
    "GPIO_10_DSI": "PANEL_BIAS_EN",   # TPS65131-Q1 ENP/ENN
    "PWM_3_DSI": "PANEL_BL_PWM",      # TPS61165-Q1 CTRL (PWM dimming)
    # Control and sequencing.
    "CTRL_PWR_EN_MOCI":  "PWR_EN_MOCI",
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    "USB_2_EN": "USB2_EN", "USB_2_OC#": "USB2_OC_N",
    # Reserved GPIO for Apple's MFi authentication coprocessor reset (TBD:
    # polarity and level come from Apple's MFi documentation).
    "GPIO_2": "MFI_RST_N",
    # 2026-10-18 (product review): LIVI powers the coprocessor from a GPIO
    # (config carPlayMfiPowerGpio; LIVI README "MFi Authentication"), so the
    # access point needs a switched supply, not just I2C and reset. GPIO_3
    # (X1 pin 210, 1.8 V) drives U15's ON pin.
    "GPIO_3": "MFI_PWR_EN",
}

# X1 pins this board deliberately does not use, outside the unused bank.
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    (-6.5 V). The same PDF's mechanical drawing header row (rendered and
    read at 400 dpi) says the opposite: 7-8 = "VDD(-6.3V)" and 10-11 =
    "VDD(+6.3V)". Feeding the wrong polarity would destroy the panel, so
    neither is assumed: the two pin groups (PANEL_PIN_A = pins 7-8,
    PANEL_PIN_B = pins 10-11) each connect to the +6.5 V and -6.5 V rails
    through a 3-pad OPEN solder jumper (JP1/JP2). Table reading: bridge
    JP1 pads 1-2 and JP2 pads 2-3. Drawing reading: JP1 2-3 and JP2 1-2.
    Confirm with TSD (or by probing a sample's FPC) BEFORE bridging
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        "LAN2_P": "DSI_D2_P", "LAN2_N": "DSI_D2_N",
        "CLK_P": "DSI_CLK_P", "CLK_N": "DSI_CLK_N",
        "IOVCC": "+1V8",
        "VPIN_A": "PANEL_PIN_A", "VPIN_B": "PANEL_PIN_B",
        "LEDA": "PANEL_BL_LEDA", "LEDK": "PANEL_BL_LEDK",
        # Panel hardware reset - GPIO_9_DSI reaches this net via X1_NETS.
        "RESET": "DSI_PANEL_EN",
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    flow(jumper, "JP1",
         "SJ3 OPEN: bridge 1-2 if datasheet TABLE is right (7-8=+6.5V), "
         "2-3 if DRAWING is - VERIFY POLARITY FIRST",
         {"A": "PANEL_VSP", "COM": "PANEL_PIN_A", "B": "PANEL_VSN"})
    flow(jumper, "JP2",
         "SJ3 OPEN: bridge 2-3 if datasheet TABLE is right (10-11=-6.5V), "
         "1-2 if DRAWING is - VERIFY POLARITY FIRST",
         {"A": "PANEL_VSP", "COM": "PANEL_PIN_B", "B": "PANEL_VSN"})
    flow(r, "R43", "100k bias-enable pulldown",
         {"1": "PANEL_BIAS_EN", "2": "GND"})
    flow(r, "R50", "100k panel-reset pulldown",
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        C10 = 7.5 uV-s / R3 -> 12 pF and 15 pF (E12).
      * BSW (load-disconnect PMOS gate) left floating - datasheet: leave
        floating if the external PMOS is not used. NC pins no-connect.
      * ENP/ENN together are PANEL_BIAS_EN (Verdin GPIO_10_DSI, 1.8 V,
        above the part's 1.4 V VIH) with a 100k pulldown, so software
        can sequence the rails after IOVCC. PSP/PSN tied low = forced PWM
        (no power-save burst ripple on the panel's analog supplies).
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        MICBIAS (2.75 V once software sets it, 5 mA max) feeds MIC_P through
        2.2 kohm; the return is held to ground by 100 ohm; both legs AC-couple
        (1 uF) into IN1P/IN1M so the return tap cancels ground noise.
      * IN2 is unused (inputs left open); GPIO1/GPIO2/GPO1/GPI1 are unused.
    Decoupling per Figure 8-1: 10 uF + 100 nF on AVDD, DREG and IOVDD, 1 uF on
    VREF and MICBIAS. ADDR to ground = I2C address 0x50.

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        "BCLK": "I2S_BCLK", "FSYNC": "I2S_FSYNC",
        "DIN": "I2S_DIN", "DOUT": "I2S_DOUT",
        "SCL": "I2C1_SCL", "SDA": "I2C1_SDA", "ADDR": "GND",
        "GPIO1": None, "GPIO2": None, "GPO1": None, "GPI1": None,
        "IN1P": "MIC_IN_P", "IN1M": "MIC_IN_N", "IN2P": None, "IN2M": None,
        "OUT1P": "AOUT_L_P", "OUT1M": "AOUT_L_N",
        "OUT2P": "AOUT_R_P", "OUT2M": "AOUT_R_N",
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    # voltage are under its MFi NDA, so no Apple footprint is drawn here:
    # J16 is a 1x6 2.54 mm header for a small daughterboard that carries the
    # coprocessor, its own LDO and any level shifting. It gets I2C_1 at
    # 1.8 V, the reset GPIO, +1V8 as the I/O reference, and MFI_5V, a 5 V
    # supply switched by U15 (TPS22918-Q1, same part and wiring as the dial's
    # U8; 2 A switch, ON VIH 1.0 V min so the 1.8 V GPIO drives it). R74
    # holds U15 off while the module is in reset (Verdin GPIOs float at
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
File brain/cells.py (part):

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

# The front end's power parts, whose copper is planned (power_route.py). In the finished board's frame, U1 at the origin
# (floorplan.py turns the whole cell 180 degrees): the two FETs one above the other with their source pins facing, so COMMON
# is about 2 mm long, and the sense resistor right under Q1, its Kelvin taps toward U1.
FET_X = -7.38            # the FETs' centre line: their courtyards end 1.2 mm from U1's, for U1's pin escapes
FET_Y = 3.89             # half a FET's courtyard: their courtyards all but touch
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            # C3 between CAP (pin 23) and VS (pin 22)
            "C3": {"CAP_CP": pull("U1", [23], 4), "LM_VS": pull("U1", [22], 4)},
            "C4": {"TMR": pull("U1", [9], 4)},
            # review 2026-11-03: VS (pin 22, MODE pin 7) through D9 with the 1 uF CVS at the pin; the HGATE dV/dt
            # network at pin 14; the ignition-latch diodes and pull-down at EN (pin 6); the input capacitor at Q2
            "C2": {"LM_VS": pull("U1", [22], 3)},
            "D9": {"LM_VS": pull("U1", [22], 4)},
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            "R4": {"IMON": pull("U1", [10], 3)},
            "R15": {"PWR_FLT": pull("U1", [12], 2)},
            # 2026-10-19: the OV/UV dividers had no pull; on six layers
            # FreeRouting left SW_SENSE (U1 pin 3) unrouted. Pulling R7 too
            # (or all four) packs the board 3.6-7.2 mm taller than 105 mm.
            "R5": {"SW_SENSE": pull("U1", [3], 4)},
        },
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        }),
    # JTAG header sits at the low-pin-number end of the Verdin odd row (its
    # JTAG pins are 1-13); the button header and its pull-ups go with the
    # reset/recovery/power pins at the other end (246-260).
    # Bring-up headers sit with the Verdin pins they serve (UART_3 pins 147/149
    # and USB_1 pins 159-165, middle of the odd row), in the bottom strip.
    # 2026-11-06: C91, the USB_1_VBUS sense filter, is at J13 and the module's pin.
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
